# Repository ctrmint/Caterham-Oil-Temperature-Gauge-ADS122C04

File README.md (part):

# Caterham Dry-Sump Oil Temperature Gauge

> **Hardware target:** Waveshare **ESP32-S3-Touch-AMOLED-1.75**, standard SKU 31261 or cased SKU 31262 (466×466 AMOLED, CO5300 controller). This firmware **does not** target the 2.1-inch RGB-LCD board, the `-1.75C` model, or the GNSS `-G` version without adaptation.

An independent **oil-temperature gauge** for the Caterham 420R dry-sump tank's resistive temperature sender (potentially Caterham part **71167**). It needs no ECU wiring and no factory gauge modifications.
- **Measurement:** an **ADS122C04 24-bit I²C ADC** drives its own 250 µA current source through a reference resistor and then the sender, and compares the voltage across each. A dedicated ground-sense wire runs to the tank. So the reading is independent of the current's accuracy, the 3.3 V rail and ground offsets.
- **Hardware:** option A is three resistors on the ADC module's pins. Option B, recommended for the car, adds two filter capacitors across the pins. Either can be built without a board, on stripboard, or on a PCB. The display runs from USB-C.
- **Display:** the Waveshare board handles display, fault reporting and alarm presentation.

**Status: bench prototype, new front end.** Host unit tests pass and the firmware compiles without warnings under ESP-IDF 5.5.5 (normal and demo builds; versions pinned in `dependencies.lock`). On the bench, so far ([docs/VALIDATION.md](docs/VALIDATION.md)):
- The firmware runs on a Waveshare 31261, and the Classic and Sweep layouts pass in the demo build. Sweep's LED and the Needle and Trace layouts (#10–#12) build and pass the host tests, but haven't been checked on the screen yet.
- With the earlier front end, a bench sender stamped 6811 followed the Bosch 0 280 130 026 curve up to 89 °C against a reference probe. That is an indication about the sender, not a calibration.

**Still owed:**
- every bench test of the ADS122C04 front end ([hardware/WIRING.md](hardware/WIRING.md), bench steps), for whichever option is built;
- the measured Rref;
- a sender calibration up to 130 °C;
- every in-car test, including the engine-running noise check.

The firmware ships **without** a validated sender temperature curve, so it **shows ohms, not °C**, until you explicitly install measured calibration points. It is **not** a primary engine-protection instrument.

## Quick start

1. Read [hardware/BOM.md](hardware/BOM.md), [hardware/WIRING.md](hardware/WIRING.md), and [docs/SAFETY.md](docs/SAFETY.md) before wiring to the car.
2. On a **bench** (not in the vehicle), wire the circuit on a breadboard as in [hardware/WIRING.md](hardware/WIRING.md):
   - the ADS122C04 module to the display's socket (3.3V, G, and I²C on GPIO17/18);
   - Rref, R1 and R2;
   - a known test resistor in place of the sender.

   Check all voltages with a meter before connecting the display board.
3. Install **ESP-IDF 5.5.5** on Fedora as described in [docs/SETUP_FEDORA.md](docs/SETUP_FEDORA.md).
4. `idf.py set-target esp32s3 && idf.py build`, then flash through the board's `/dev/serial/by-id/usb-Espressif_*` port, never a bare `/dev/ttyACM0`, which can be another USB device: `idf.py -p "$(ls /dev/serial/by-id/usb-Espressif_*)" flash monitor` (see [Connect the board and flash](docs/SETUP_FEDORA.md#connect-the-board-and-flash)).
5. Boot with an **uncalibrated** sensor and confirm the display shows resistance and `CALIBRATION REQUIRED`; simulate open and short faults on the bench.
6. Independently characterise the exact sender, generate `main/CalibrationData.h`, rebuild, and verify °C against a reference thermometer. See [docs/CALIBRATION.md](docs/CALIBRATION.md).
7. For the car, solder the same parts to the module, fit the terminal strip and the box ([hardware/WIRING.md](hardware/WIRING.md), "Building it without a board"), and pass the bench steps, including the short-to-battery test. Then do the power, grounding, thermal, EMI and installation checks in [docs/INSTALLATION.md](docs/INSTALLATION.md).

`./scripts/test_host.sh` runs the host tests without any ESP32 hardware: the conversion, fault, alarm and display logic, the ADC's frame and CRC decoding, a circuit simulation of both front-end options, the stripboard and PCB checks, the calibration tool and the sender graph. GitHub Actions ([CI workflow](.github/workflows/ci.yml)) runs them, plus the normal and demo firmware builds, on every pull request and every push to `main`. `idf.py menuconfig` → **Caterham oil temperature gauge** → **Display synthetic sensor readings** runs a clearly marked BENCH DEMO; it must remain **off** for a real vehicle.

## Interface hardware

The front end is small enough to need no interface board. **Option A** is three resistors soldered to the Adafruit ADS122C04 module, with a 3-way terminal strip for the harness, all in a small box beside the display. **Option B**, recommended for the car, adds two 47 nF capacitors across the module's analogue pins. They filter interference near the ADC's 256 kHz sampling rate, and a shorted one gives a fault rather than a reading.

Each option has its own folder: [hardware/option-a](hardware/option-a/README.md) and [hardware/option-b](hardware/option-b/README.md). Each folder has:
- a description of the design;
- a complete parts list;
- a checked stripboard layout;
- a two-layer PCB, as a KiCad project with Gerbers.

[hardware/WIRING.md](hardware/WIRING.md) has the circuit, the build without a board and the bench steps.

| Part | Where | Why |
|---|---|---|
| Rref, 2.00 kΩ 0.1 % ≤ 25 ppm/°C | A0 to the sender wire | Carries the ADC's 250 µA current to the sender; the voltage across it is the reference. Set `kReferenceOhms` in `main/Config.h` to its measured value |
| R1, 2.2 kΩ | A1 to the sender wire | Sender high side. Limits fault current |
| R2, 2.2 kΩ | A2 to the ground-sense wire | Sender low side. Limits fault current |

The display runs from its own USB-C socket (in the car, an ignition-switched USB-C charger), and the module takes the display's 3.3 V. The harness is three wires: signal, ground sense, and a return wire from the gauge's ground to the tank bond stud.

## Display

There are twelve layouts of the same readings. Every one is on a pure black background (`#000000`), apart from White's white face, so the AMOLED's unused pixels are switched off.

* **Classic:** the title reads `OIL °C`, `OIL °F` or `OIL ohm`. The reading itself has no unit: large fixed-width digits, right-aligned so the ones digit stays in place, with a 3-digit reading centred on the screen (a four-character one such as `>284` or a 4-digit resistance uses the full width). The bottom line reads like `MAX 112  |  123 ohm` (maximum, then the sender resistance).
* **Sweep:** a 40-segment ring around the edge covering 30–130 °C, with scale labels 30…130 (86…266 in °F). Each lit segment shows the colour of its own place on the scale. Three large seven-segment digits, centred, sit over faint ghost segments; beyond the table a `<` or `>` sign appears just left of them. The unit sits above `OIL TEMP`, with the status, footer and demo text below. A resistance of 1000 Ω or more (uncalibrated only) shows as `--` in Sweep, and in full in Classic.
  * **The LED:** a round light at 6 o'clock, in the open bottom of the ring. It glows in the reading's colour and pulses while an alarm is latched: slowly at amber (`HIGH TEMPERATURE`, from 115 °C after the 2.5 s debounce) and faster at red. It's off on a sensor fault and in an uncalibrated build. The exception is a brief fault while an alarm is latched: the LED keeps pulsing, as the digits keep the alarm colour.
* **Needle:** an analogue dial. A white scale runs from lower left to lower right over 30–130 °C, with five numbers (30, 55, 80, 105, 130; 86…266 in °F), a tick between each pair and a pointer at each number. A red needle sits under a dark hub, with `OIL` above the unit at the bottom. There's no digital readout. The needle follows the same rules as Sweep's segments. It's hidden on a fault or when uncalibrated, rests at the start below the table, and sits at the table maximum above it. It moves smoothly, never past the reading, and doesn't sweep at power-up.
* **Trace:** the last 60 s, one point a second, newest on the right, as a thick line in the colours of the temperatures that made it: each point's colour, the same as the digits' at that moment, carries into the line around it. The newest point is a dot in its colour, or a ring when it's beyond the table. The window is 30 °C tall, with grid lines every 10 °C. It moves only when the newest point comes within 3 °C of its top or bottom, then re-centres. Thin amber and red lines mark 115 °C and 130 °C when they're in view. A fault or a reading below the table leaves a gap, never a carried-over value. The LED from Sweep sits at 6 o'clock under the status lines, with the same colours and pulses. There's no digital readout and, uncalibrated, no trace. The history is kept whichever layout is showing, and starts empty at power-up.
* **Tape:** an aircraft-style moving scale. The tape scrolls past a fixed pointer, so the scale moves rather than the needle. It shows 40 °C at a time, with ticks every degree and numbers every 10. A strip down its edge is in each temperature's colour, and amber and red bars mark 115 °C and 130 °C, so the hot zones come into view before the oil gets there. Past the ends of the calibration table the tape is hatched, with no numbers, and a small marker shows the session maximum. The reading sits in a window by the pointer: `>130` beyond the table, `--` on a fault, and ohms when uncalibrated. Under it is the rate of change, such as `▲ 2.4 °C/min`, `▼ 1.1 °C/min` or `STEADY` (under 0.5 °C/min). The rate comes from the last 30 one-second samples and is hidden unless all 30 are clean readings inside the table. The tape eases to each reading and is hidden on a fault or when uncalibrated.
* **OEM:** styled on the Caterham factory gauges. A black face in a dark rim, with a short grey tick every 10 °C from 50 to 130 °C and four numbers, 70, 90, 110 and 130 (158…266 in °F), mapped one for one onto the factory oil-pressure gauge's 0–8 bar. 90 is at 12 o'clock with the unit under it, and 50 has a tick but no number. An off-white tapered needle with a counterweight sits under a black hub. It follows Needle's rules on this span, so it rests at the start below 50 °C and below the table, sits at the end above it, and is hidden on a fault or when uncalibrated. It doesn't drop to the stop on a fault, because a resting needle would look like cold oil. There's no digital readout.
  * **The oil symbol is the LED:** an oil can with a thermometer below the hub, lit in the reading's colour and pulsing with the alarm, exactly as the LED on Sweep and Trace. It's dark grey when the LED would be off.
  * **CATERHAM:** the word shows at the bottom only while all is well: `NORMAL` or `OIL WARMING`, no alarm latched, a calibrated build that isn't the demo. Anything else (an alarm, a fault, a reading beyond the table, no calibration) puts the status line and footer in its place, so the dial changes visibly the moment something needs attention. The demo build never shows it.
* **White:** styled on a white-faced aftermarket oil-temperature gauge. A white face in a black ring, with a black tick every 2 °C from 40 to 140 °C (long at each 20, medium at the other tens) and six numbers, 40, 60, 80, 100, 120 and 140 (104…284 in °F), with 90 at 12 o'clock. A red tapered needle with a short counterweight sits under a black hub, with `OIL` and the unit below it. The needle follows Needle's rules on this span: it rests at the start below 40 °C and below the table, sits at the table maximum above it, and is hidden on a fault or when uncalibrated. There's no digital readout.
  * **The LED:** the same LED as on Sweep and Trace, at 6 o'clock in a round black socket, so its colours and glow show against the white. When it's off, the socket shows a dark-grey lens.
  * **The status window:** a black window at the bottom, running down into the ring, with the status line and footer in their usual colours. It shows only when something needs attention, which is exactly when OEM would hide `CATERHAM`, so the face stays clean while all is well. The demo build always shows it.
  * **Brightness:** a white face is much brighter than the dark layouts, especially at night. The firmware has no brightness control, so long-press to Night, or another dark layout, if it dazzles.
* **Night:** a dark layout for driving at night, with no ring, face or ticks. It's quiet while all is well and lights up the moment anything needs attention. The reading is at the centre of the screen in both states.
  * **Quiet:** while all is well (exactly when OEM shows `CATERHAM`), only the reading shows: whole degrees in a small font, in its usual colour at half brightness, with a dim unit under it. Under that, a small dim dot rises and falls every 2 s. It steps once per display update, so if the updates ever stopped the dot would stop too: a dark screen can't pass for a live one.
  * **Lit:** anything else (an alarm, a fault, a reading beyond the table, no calibration, and always in the demo build) shows Classic's large digits at full brightness with `OIL °C` above them, the status line and footer below, and the LED from Sweep and Trace under them. The status goes to `HIGH TEMPERATURE` at 115 °C, before the alarm's 2.5 s debounce, so the screen lights at the threshold.
* **Nixie:** the reading in four glowing nixie tubes, right-aligned in the same cells as Classic, so a 3-digit reading leaves the first tube dark. The numerals are drawn as thin glowing wires, always nixie orange, with the ten unlit numerals faint behind them as in a real tube. `<`, `>` and `-` are drawn the same way, and anything the tubes can't show is `--`. `OIL °C` sits above the tubes, with the status line, the footer and the LED from Sweep and Trace always shown below. Nixie orange is close to the alarm amber, so on this layout the status line (in the reading's colour) and the LED carry the colour, not the numerals.
* **Heritage:** a dial in the spirit of a 1960s instrument. A chrome-look bezel (lit from the upper left), a black face, and cream ticks and numbers on a short 90° sweep across the top: 50–130 °C, a tick every 5 °C (long at each 20), with 50, 90 and 130 numbered (122, 194, 266 in °F) and 90 at 12 o'clock. A slim cream needle with a short counterweight turns about a pivot below the centre, under a black boss with a chrome cap. It follows Needle's rules on this span, as OEM's does, and never points below the pivot. There's no digital readout.
  * **Under the pivot:** `OIL TEMP` and the unit while all is well, exactly as OEM shows `CATERHAM`, or the status line and footer in their place whenever anything needs attention.
  * **The lamp:** the LED from Sweep and Trace at 6 o'clock in a chrome surround, with a dark lens when it's off.
* **Track:** a data page for track days. At the top, the reading in its colour, with `MAX 121` (the session maximum, or `MAX >130` once it went above the table) and the rate of change (as on Tape) beneath it. Then a row for each band since power-up, each with a bar in the band's colour and the time spent there:
  * `<60`, `60-115`, `115-130`, `130+` (from the alarm thresholds; `<140`, `140-239`, `239-266`, `266+` in °F) and `--`, which is time with no temperature known: a fault, or a gap of more than 2 s between readings. A reading beyond the table counts towards the coldest or hottest band.
  * Each bar is its band's share of the time since power-up, so the bars add up to one full bar. Any time at all in a band shows as at least a sliver. Times read `m:ss`, then `1h05`, up to `99h59`. They start again from zero at each power-up and are counted whichever layout is showing.
  * The status line, the footer and the LED from Sweep and Trace sit below. Uncalibrated, only the ohms and the status show: no rows, no MAX and no rate.
* **Warm-up:** for the first minutes of a drive. A 270° ring like Classic's arc fills from 0 °C to the 60 °C warm threshold in the reading's colour, so it's full once the oil is warm and turns amber or red with the reading. Classic's large digits sit in the middle with `OIL °C` above, and the status line and footer below. There's no LED.
  * **The warm-up line:** while warming, the time since power-up and the rate of warming (as on Tape), such as `2:35    ▲ 3.1 °C/min`. At the first reading of 60 °C or more it becomes `WARM IN 6:12`, which stays for the rest of the power cycle even if the oil cools again. If the oil was already warm when the gauge started, it shows `WARM AT START`.
  * **On a fault the ring disappears altogether.** An empty ring would look like cold oil. Below the table the ring shows its empty track, because the oil is known to be cold. It never predicts when the oil will be warm. Uncalibrated, there's no ring and no warm-up line.

The status line and the footer are on every layout, so alarms and faults always show as text. On OEM they take the wordmark's place, on Heritage the legend's, on White they appear in a black window, and Night lights up with them, whenever anything needs attention.

**Colours:** the digits (except Nixie's, which are always nixie orange), the status text and Classic's arc are graduated by temperature, blending smoothly between bands: dark blue below 50 °C, light blue 50–69, green 70–95, yellow 96–105, amber 106–119 and red from 120 °C. The colour is never less severe than a latched alarm (amber at 115 °C, red at 130 °C, unchanged). A fault or an uncalibrated reading is amber.

Beyond the calibration table the reading shows `<min` or `>max` (for example `<20` or `>140`) and no temperature reading, and the unit stays in the label. Uncalibrated firmware shows `ohm` in every layout. There are no scale numbers, no lit segments, no LED (OEM's symbol stays dark grey, and White's socket and Heritage's lamp show their dark lens), no needle, no trace, no tape or rate, no Track rows, and no Warm-up ring or warm-up line.

**Changing layout:** press anywhere on the screen for at least 1 s (a long-press). Each press moves to the next layout: Classic, Sweep, Needle, Trace, Tape, OEM, White, Night, Nixie, Heritage, Track, Warm-up, then Classic again. A short tap or a swipe does nothing. The choice is stored in flash and restored at power-up; it is Classic on first boot, or if the stored choice is missing or can't be read.

**Choosing °F:** `idf.py menuconfig` → **Caterham oil temperature gauge** → **Display temperature unit**, then rebuild. °C is the default. The unit applies to the display only; the serial CSV log stays in °C.

## Wi-Fi

The gauge can join a Wi-Fi network or host it. It's off until you ask for it, and it can't delay a reading or touch the alarms: everything Wi-Fi runs in its own task below the measurement loop's priority.

* **One network, two ways:** when Wi-Fi is switched on, the gauge looks for the network named in `main/wifi_secrets.h`.
  * **Found:** it joins as a client. The panel shows `Joined <network>` and the address it was given.
  * **Not found:** it hosts that network itself, with the same name and password, at `192.168.4.1`. The panel shows `Hosting <network>`. A laptop set up for that network connects either way.
  * **Found but it can't join** (a wrong password, say): `Wifi failed` and `Can't join <network>`. It never hosts a second network with the same name.
  * **A joined network that drops** (driving away from home, say): it rejoins if it can, and hosts the network once it's gone.

* **The BOOT button** (the top side button) switches it. Each short press moves to the next state, and a black panel across the top of the screen confirms it for 3 s:
  * `Wifi Off` → `Wifi - Web On, UDP Off` → `Wifi - Web On, UDP On` → `Wifi - Web Off, UDP On` → `Wifi Off`.
  * States for features that aren't built in are skipped. With only the UDP stream built, presses go `Wifi Off` ↔ `Wifi - Web Off, UDP On`; with only the web page, `Wifi Off` ↔ `Wifi - Web On, UDP Off`.
  * While starting, the panel says `Wifi starting...` and `Looking for <network>`. Once up, it says `Joined` or `Hosting`, with the network and the gauge's address. `Wifi failed` shows in amber if it can't start.
  * The panel never covers the status lines or the LED on any layout, and the button never touches an alarm.
  * The state is saved and restored at power-up. A long press does nothing. Don't hold BOOT while powering up, or the board starts in flashing mode.
* **The web log page** (#32): open `http://<the address on the panel>/` in a phone's browser on the same network (`http://192.168.4.1/` when the gauge hosts it). It shows the live reading on a copy of the Sweep face, a chart of the session with the alarm thresholds, the time in each band, and a **Download CSV** button. It loads nothing from the internet, can't change anything on the gauge, and keeps its copy of the session on the phone through reloads and gauge restarts. The gauge keeps the last 8 hours for it from power-up. See [docs/WEB_PAGE.md](docs/WEB_PAGE.md).
* **The UDP data stream** (#33): four packets a second to the multicast group `239.10.10.10:5005`, send-only, for a laptop or Raspberry Pi on the network. Watch it with `python3 scripts/udp_listen.py`, a live terminal dashboard (add `--csv FILE` to log, or `--plain` for one line per packet). The packet format is in [docs/UDP_STREAM.md](docs/UDP_STREAM.md).
* **Setting it up:**
  1. Copy `main/wifi_secrets.example.h` to `main/wifi_secrets.h` and put in the network name (1–32 characters) and password (8–63, WPA2). Git ignores that file: never commit it.
  2. `idf.py menuconfig` → **Caterham oil temperature gauge** → **Wi-Fi (#32, #33, #34)** → switch on **Web log page**, **UDP data stream**, or both.
  3. Rebuild. A first build after creating the file picks it up by itself.

  Without the file, or with both off, a build never starts Wi-Fi. The button then says `Wifi failed - no settings` or `Wifi not built`.

Every output, from the display and the serial log to the UDP packet and the page's JSON and CSV, is listed side by side, with how each writes the same values, under [Outputs in docs/ARCHITECTURE.md](docs/ARCHITECTURE.md#outputs).

## Repository structure

```text
.
├── main/
│   ├── main.cpp                    # main sampling / display loop
│   ├── Config.h                    # reference resistor value, fault and warning settings
│   ├── CalibrationData.h           # fail-closed uncalibrated default
│   ├── core/                       # platform-independent resistance & temp math,
│   │                               # ADC frame/CRC decoding (AdcFrame.h),
│   │                               # plus display text (DisplayText.*), sweep ring,
│   │                               # LED and needle model (SweepModel.*), the trace's
│   │                               # history (TraceModel.*), the tape and rate of change
│   │                               # (TapeModel.*), the OEM and White dials
│   │                               # (OemModel.*, WhiteModel.*), Night's quiet
│   │                               # rule and heartbeat (NightModel.*), Nixie's
│   │                               # tubes and numerals (NixieModel.*), the
│   │                               # Heritage dial (HeritageModel.*), Track's
│   │                               # band times and bars (TrackModel.*), the
│   │                               # warm-up ring and clock (WarmupModel.*), the
│   │                               # UDP packet (UdpPacket.*), the web page's
│   │                               # log and JSON (WebLog.*), the Wi-Fi button
│   │                               # and panel (WifiChoice.*)
│   │                               # and layout choice/long-press
│   │                               # (LayoutChoice.*)
│   ├── hal/Ads122c04Source.*       # ADS122C04 over I²C (port 0, GPIO17/18)
│   ├── net/WifiNet.*               # the Wi-Fi network and UDP stream task (#33, #34)
│   ├── net/WebServer.*             # the web page's log, status and server (#32)
│   ├── web/index.html              # the web page, built into the firmware (#32)
│   ├── display/GaugeDisplay.*      # Waveshare BSP + LVGL 9 gauge; layout switching
│   │   ├── ClassicLayout.cpp       # Classic layout
│   │   ├── SweepLayout.cpp         # Sweep layout, with its LED
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
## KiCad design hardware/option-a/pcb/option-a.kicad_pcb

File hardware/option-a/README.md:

# Option A: the minimal front end

Option A is the simplest version of the gauge's front end: the ADS122C04 module's own current source, a reference resistor and two tap resistors. There's nothing else, so it needs no PCB at all, although a stripboard layout and a PCB are here too.

It's fine on the bench. **For the car, use [option B](../option-b/README.md)** unless option A passes the in-car noise check (step 14 in [WIRING.md](../WIRING.md)). Option B adds two filter capacitors and keeps everything else the same, including the firmware.

## The circuit

| Module pin | Connects to | Part |
|---|---|---|
| VIN, GND, SDA, SCL | the display's `3.3V`, `G`, `17`, `18` | the display lead |
| A0 | `SENDER`, through Rref | **Rref: 2.00 kΩ, 0.1 %, 25 ppm/°C or better** |
| A1 | `SENDER`, through R1 | R1: 2.2 kΩ, 1 % |
| A2 | the ground-sense wire, through R2 | R2: 2.2 kΩ, 1 % |
| A3, Ref+, Ref−, DRDY, !RST | nothing | |

**How it measures:**
- The ADC drives 250 µA out of A0, through Rref and then the sender, to the tank. It reads the voltage across each.
- The resistance is `Rs = Rref × Vs / Vref`. The current's ±6 % accuracy, the ADC's reference and the 3.3 V rail all cancel, so the reading is as good as Rref.
- **Measure Rref** and put its value in `kReferenceOhms` (`main/Config.h`).
- The ground-sense wire reads the tank's own potential, so a ground offset between the gauge and the tank cancels too.

**Faults:** every open joint, broken wire and short shows a fault, never a reading. The ADC's 10 µA burn-out source checks both taps every cycle. [WIRING.md](../WIRING.md) has the full list, the engineering calculations and the bench steps.

**What option A doesn't have:**
- **No input filter.** Interference near the ADC's 256 kHz sampling rate can reach the reading without a fault. Option B fixes this.
- **No clamp diodes or TVS.** At least 2 kΩ between every harness wire and the ADC holds a short to 14.4 V to about 5 mA per pin, within the chip's rating. That isn't load-dump protection, so the short-to-battery bench test (step 12) is owed.

## Three ways to build it

| Build | What it is | Where |
|---|---|---|
| **Without a board** | The three resistors soldered straight onto the module's pins, with a 3-way terminal strip for the harness | [WIRING.md](../WIRING.md), "Building it without a board" |
| **Stripboard** | 73.7 × 27.9 mm (28 holes × 10 strips): 11 track cuts, 3 wire links, two screw terminal blocks | [veroboard/](veroboard/): `layout.svg` and `ASSEMBLY.md` |
| **PCB** | 71 × 36 mm, two layers, plated through-hole, Micro-Fit connectors that lock | [pcb/](pcb/): the KiCad project, `fab/option-a-gerbers.zip` and renders |

[BOM.md](BOM.md) lists the parts for all three: the parts every build needs, then each build's own.

In every build, the module is **soldered in by its header pins, never socketed**, and Rref is measured before it goes in.

### Stripboard

- **J1, the display lead:** 1 3.3V, 2 G, 3 18 (SCL), 4 17 (SDA). The four strips run straight to the module's own pins.
- **J2, the sender harness:**
  - 1 signal wire to the sender;
  - 2 ground-sense wire;
  - 3 **empty**;
  - 4 return wire to the tank bond stud.
- **Upgrading:** option B's C1 and C2 holes (13,4–13,5 and 15,5–15,6) are left empty, so fitting the two capacitors turns this board into option B.

### PCB

- **J1, the display lead (Micro-Fit 2x3):**
  - 4 SDA (17), 5 SCL (18) and 6 3.3V each sit beside a ground (pins 1–3);
  - the three ground wires join at the display plug's `G` pin;
  - J1's grounds reach the module on the top copper, over the signal tracks.
- **J2, the sender harness (Micro-Fit 1x4):** the same as the stripboard's J2, with pin 3 empty.
- **Mis-plugging:** J1 and J2 are different sizes, so neither cable fits the other's header.
- **Mounting:** four M3 holes, 64 × 29 mm apart, and M2.5 nylon standoffs under the module's own holes.
- **Upgrading:** this board has no C1 or C2 pads. For option B, order the [option B PCB](../option-b/pcb/).

## Why the boards look the way they do

- **Return wire:** it lands on the board's ground, so the display lead needs only its four signals. The no-board build needs a fifth wire for it.
- **J2 pin 3 is empty, and no ground copper runs beside A1, A2, SENDER or SENSE.** A solder bridge from any of those to ground would give a believable wrong reading, not a fault. Two examples:
  - **SENSE to ground:** the tank offset adds straight into the sender's voltage.
  - **A1 to ground:** the measurement turns single-ended.

  The stripboard checker refuses a ground strip beside them. On the PCB, a DRC rule keeps their copper at least 1 mm from ground, and there's no ground pour; the closest they actually come is 2.5 mm.
- **R1 meets SENDER at J2 pin 1** by its own track, so it senses at the connector, not partway along the excitation current's path.

## Before you trust it

1. Measure Rref, and set `kReferenceOhms`.
2. Run bench steps 1–13 in [WIRING.md](../WIRING.md), including the tap checks, the pin-pair shorts and the short to battery.
3. Do the in-car noise check (step 14).
4. Calibrate the sender ([CALIBRATION.md](../../docs/CALIBRATION.md)).

Until then it's a bench prototype ([VALIDATION.md](../../docs/VALIDATION.md)).

## Files

Everything here except this README is generated by `scripts/boards/build.sh`, from `scripts/boards/`. That script runs KiCad 10.0.8 in its container (podman or docker).
- **The layouts:**
  - the circuit is `circuit.py`;
  - the stripboard is `vero_layout.py`;
  - the PCB placement and routing are `pcb_layout.py`.
- **Each build:**
  - checks the stripboard layout;
  - runs KiCad's ERC, and DRC with schematic parity;
  - confirms the schematic's netlist is the circuit;
  - writes `outputs.sha256`.
- **Tests:** `tests/test_boards.py` fails if any output is stale, and re-checks the circuit, the stripboard and the PCB's clearances independently.
- **Editing:** never edit the outputs by hand.

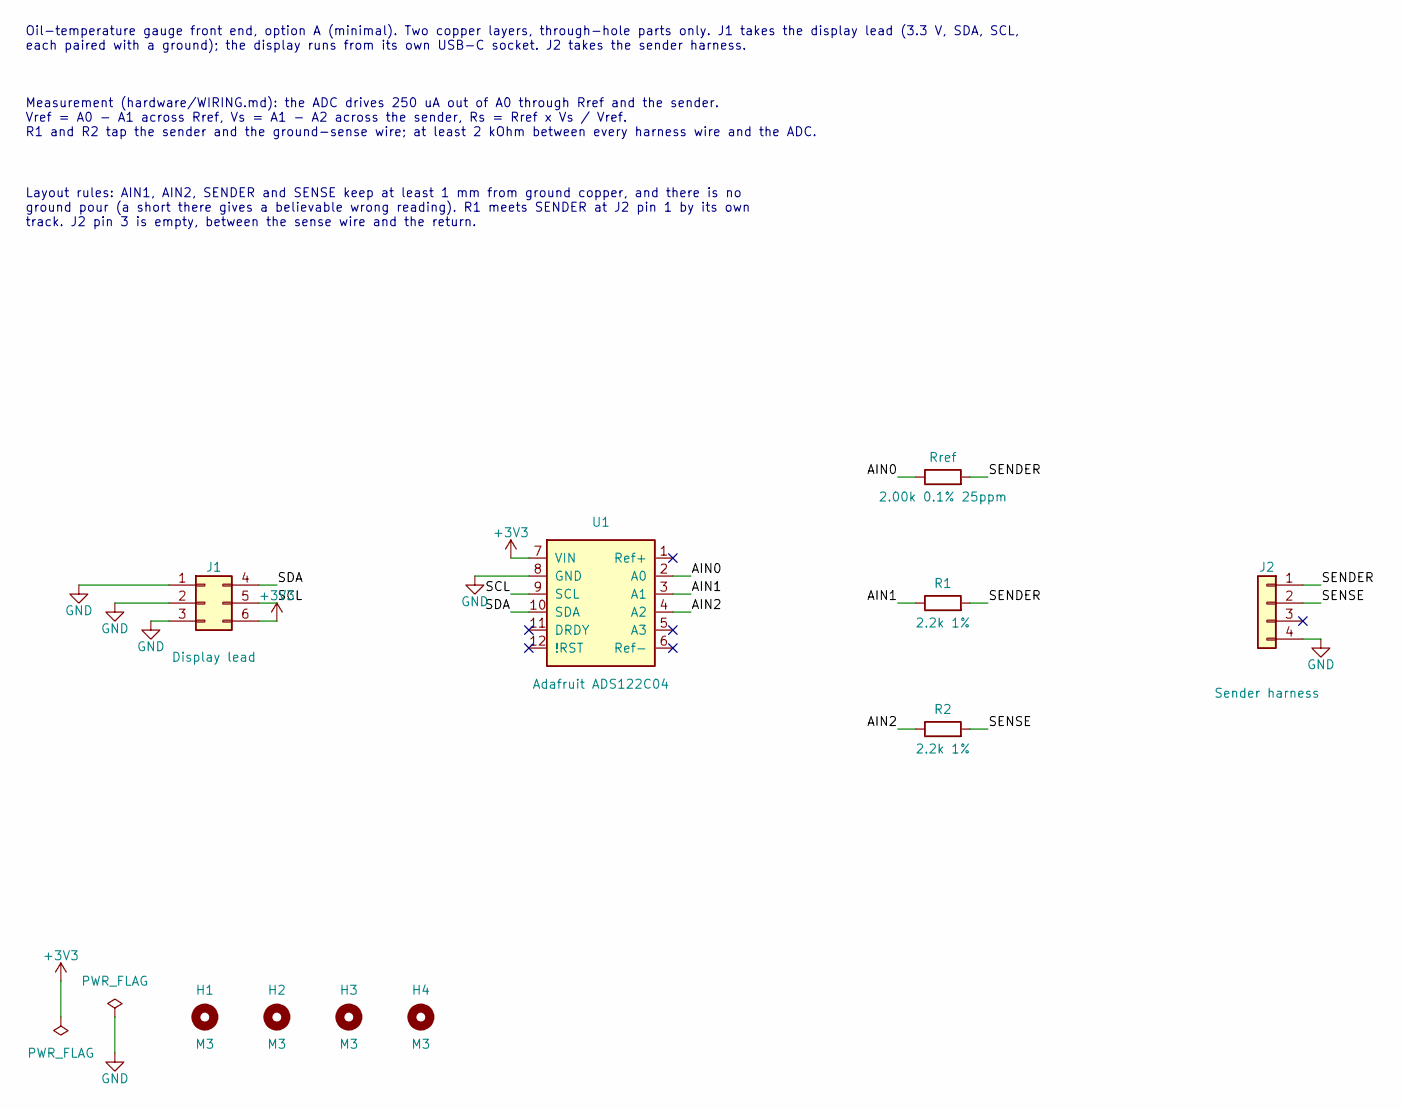
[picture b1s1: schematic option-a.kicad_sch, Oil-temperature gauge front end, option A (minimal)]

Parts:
H1, H2, H3, H4: M3; MountingHole_M3
J1: Display lead; MicroFit_2x03_RA; MPN 43045-0600; DigiKey_UK WM1815-ND
J2: Sender harness; MicroFit_1x04_RA; MPN 43650-0400; DigiKey_UK WM1862-ND
R1, R2: 2.2k 1%; R_P10.16mm
Rref: 2.00k 0.1% 25ppm; R_P10.16mm
U1: Adafruit ADS122C04; Adafruit_ADS122C04; MPN 6432

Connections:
+3V3: J1.6, U1.7 (VIN)
/AIN0: Rref.1, U1.2 (A0)
/AIN1: R1.1, U1.3 (A1)
/AIN2: R2.1, U1.4 (A2)
/SCL: J1.5, U1.9 (SCL)
/SDA: J1.4, U1.10 (SDA)
/SENDER: J2.1, R1.2, Rref.2
/SENSE: J2.2, R2.2
GND: J1.1, J1.2, J1.3, J2.4, U1.8 (GND)

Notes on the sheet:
Oil-temperature gauge front end, option A (minimal). Two copper layers, through-hole parts only. J1 takes the display lead (3.3 V, SDA, SCL, each paired with a ground); the display runs from its own USB-C socket. J2 takes the sender harness.
Layout rules: AIN1, AIN2, SENDER and SENSE keep at least 1 mm from ground copper, and there is no ground pour (a short there gives a believable wrong reading). R1 meets SENDER at J2 pin 1 by its own track. J2 pin 3 is empty, between the sense wire and the return.
Measurement (hardware/WIRING.md): the ADC drives 250 uA out of A0 through Rref and the sender. Vref = A0 - A1 across Rref, Vs = A1 - A2 across the sender, Rs = Rref x Vs / Vref. R1 and R2 tap the sender and the ground-sense wire; at least 2 kOhm between every harness wire and the ADC.

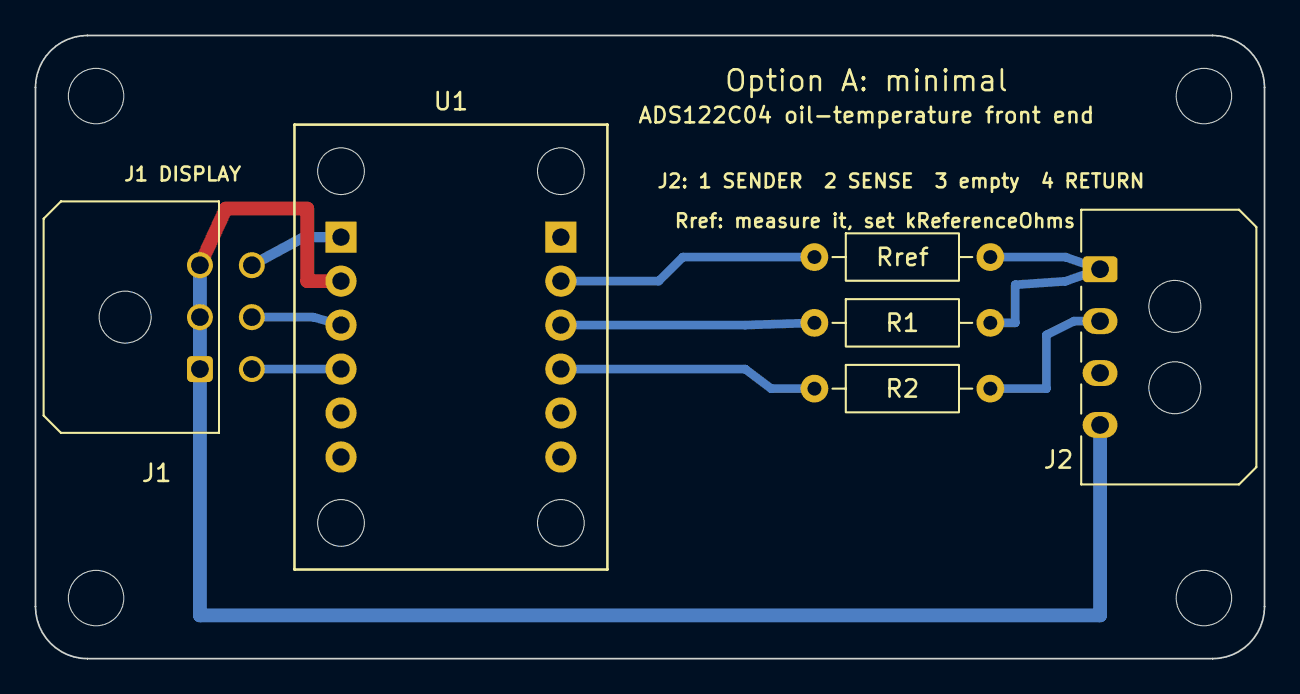
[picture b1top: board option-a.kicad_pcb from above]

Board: 2 copper layers, 71.0 x 36.0 mm, 10 parts (0 on the bottom side), 9 nets.

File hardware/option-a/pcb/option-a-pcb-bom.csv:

Qty,Ref,Item,Manufacturer,MPN,Digi-Key UK,Notes
1,U1,ADC module,Adafruit,6432,,ADS122C04 24-bit I2C ADC module (The Pi Hut SKU ADA6432). Solder it in by its header pins; never socket it
1,Rref,Reference resistor,,,,"Rref: 2.00 kOhm, 0.1 %, 25 ppm/C or better, metal film, 0.25 W, 0207. Measure it and put the value in kReferenceOhms"
2,"R1, R2",Tap resistors,,,,"2.2 kOhm, 1 %, metal film, 0.25 W, 0207"
1,,Display,Waveshare,ESP32-S3-Touch-AMOLED-1.75,,"Standard or -B; not 1.75C, 2.1 LCD or GNSS -G. Check the board revision and socket first"
1,,Display plug,Samtec,TSW-108-07-G-S,,8-way 2.54 mm gold pin header: the plug for the display case socket
1,,Display power,,,,"Ignition-switched USB-C charger rated for the car's transients, and a secured USB-C lead. Never 12 V to the display"
as needed,,Harness wire,,,,"0.5 mm2 (20 AWG): signal, ground sense and return, twisted together, away from ignition leads, the alternator and the exhaust"
1,,Ring terminal,,,,For the tank bond stud: the ground-sense and return wires land on it
1,,Sender spade connector,,,,"Insulated, retained against vibration; check it fits the sender"
1,,Box,,,,"Small, insulated, with strain reliefs or glands for both cables"
-,,Heat-shrink and sleeving,,,,For the harness and display-lead joints
1,,Sender,,,,The car's existing resistive oil-temperature sender (dry-sump tank). Confirm its type before relying on it
1,,PCB,,,,"Order from pcb/fab/option-a-gerbers.zip: 2 layers, 1.6 mm FR-4, 1 oz copper, plated holes, any standard prototype service"
1,J1,Display header,Molex,43045-0600,WM1815-ND,"Micro-Fit 3.0 2x3 right-angle header, tin, board lock"
1,,Display lead housing,Molex,43025-0600,WM1785-ND,Micro-Fit 3.0 2x3 receptacle housing (mates with J1)
1,J2,Harness header,Molex,43650-0400,WM1862-ND,"Micro-Fit 3.0 1x4 right-angle header, tin"
1,,Harness housing,Molex,43645-0400,WM1847-ND,Micro-Fit 3.0 1x4 receptacle housing (mates with J2)
9 (+spares),,Crimp terminals,Molex,43030-0007,WM1837-ND,"Micro-Fit 3.0 female crimp terminal, tin, 20-24 AWG"
1,,Crimp tool,Molex,63819-0000,,Micro-Fit 3.0 hand crimp tool (or a Micro-Fit ratchet crimper)
12,,Module header pins,,,,"2.54 mm header, both rows; a strip comes with the module"
1,,Display lead,,,,"3 twisted pairs, 24 AWG stranded, 20 cm or less: 3.3V+GND, SCL+GND, SDA+GND. The three grounds join at the display plug's G pin"
4,,Module standoffs,,,,"M2.5 x 2.5 mm nylon spacers with M2.5 nylon screws and nuts, under the module's four holes"
4,,Board screws,,,,"M3, into the box's bosses (holes 64 x 29 mm apart)"

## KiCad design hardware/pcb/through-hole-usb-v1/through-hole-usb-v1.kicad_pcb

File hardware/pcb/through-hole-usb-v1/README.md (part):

# through-hole-usb-v1: interface PCB

through-hole-usb-v1 is the third interface PCB (issue #54). It's [through-hole-v1](../through-hole-v1/README.md) without the 12 V supply: the display runs from its own USB-C socket, and this board takes its 3.3 V from the display over the cable.
- **One copper layer, through-hole parts only,** all hand-soldered.
- **It lives in its own 3D-printed box,** and a cable connects it to the display. The display doesn't plug into it.
- **It carries the same measurement and protection** as the other two boards.
- **A dedicated ground return comes back from the tank** on the harness connector, because a USB supply needn't share the car's ground (see Grounds, below).

**The firmware is unchanged:** the same ADS1115, address 0x48, GPIO17/18 and inputs.

**Status:** designed, with zero ERC and zero DRC findings. Not yet built or tested; the checks owed are listed below. Like the rest of the gauge, it's supplementary to the factory warnings ([docs/SAFETY.md](../../../docs/SAFETY.md)).

| | |
|---|---|
| Size | 65 × 62 mm, 3 mm corner radius, 4 × M3 mounting holes |
| Copper | **One layer** (bottom), 1 oz, ground pour. No vias, no top copper. |
| Tracks | 0.5 mm signals, 0.6 mm 3.3 V and the sender wire, 0.8 mm grounds; 0.3 mm minimum clearance |
| Pads | At least 0.6 mm of copper round each hole, because a single-sided board has unplated holes |
| Resistors | All lie flat at 10.16 mm: Vishay's MBB0207 datasheet asks for at least 10.0 mm between the leads |
| Parts | 24 through-hole parts plus 4 mounting holes. One part is the Adafruit ADS1115 module, soldered in. |
| Connectors | Two Molex Micro-Fit 3.0 right-angle headers, both along one edge, so both cables leave through one wall of the box |

## What's on it

- **ADC (U1):** the Adafruit ADS1115 breakout (product 1085).
  - The ADS1115 itself only comes in surface-mount packages, so the board takes the module.
  - Solder the module in by its header pins and hold it with nylon standoffs at its four holes. **Never socket it:** a lifting socket contact caused #39.
  - The module brings its own 10 kΩ I²C pull-ups and the 10 kΩ ADDR pull-down (address 0x48). Its A− (the ADC's ground) is joined to GND on the module.
- **Measurement and protection:** [WIRING.md](../../WIRING.md), with PR #34's protection, exactly as on through-hole-v1.
  - **Rp (R1)** is 470 Ω, 0.1 %, 25 ppm, 0.4 W.
  - **R2** is a Kelvin connection on Rp's top pad, on its own track.
  - **Each harness tap is two stages,** 1 kΩ then 1N4148 clamps to 3.3 V and GND then 1 kΩ: R3, D1, D2, R4 for A3, and R5, D3, D4, R6 for A1.
  - **D5** is a P6KE18A TVS on the signal wire.
  - **R7** is the 100 kΩ break-detect bias, on the harness side.
  - **C1–C3** are 100 nF C0G filters to ground.
  - Nothing is in series between Rp and the sender pin.
  - `tests/test_through_hole_usb_v1.py` checks all of this against the design table.
- **3.3 V:** it comes from the display on the cable. There's no 5 V on the cable and no regulator on the board.
  - A harness fault's current goes into the display's 2 A rail, which absorbs it, as on the other boards. With a wire at 14.4 V, that's about 34 mA (signal) or 10 mA (sense).
  - R8/R9 (3.3 kΩ) strengthen the I²C pull-ups for the cable, and C4 decouples 3.3 V at the module.
- **Test points:** TP1 and TP2 are grounds, TP2 on the track from the harness return; TP3 is 3.3 V.

## Power and grounds

**Power.** The display's own USB-C socket powers everything.
- In the car, use a USB-C charger (5 V, 1 A or more) on an **ignition-switched** 12 V circuit, so the gauge turns off with the ignition.
- On the bench, a USB-C supply or a laptop will do. Never connect the harness to the car while a laptop powers the display.
- Don't feed anything into the display's 5V pin: it's joined to the display's USB-C supply.

**Grounds.** On the other boards, the gauge's supply ground is wired to the chassis near the tank bond, and that carries the sender's current back. A USB supply makes no such promise: a power bank floats, and a car USB-C charger reaches the chassis only through its 12 V socket's wiring, somewhere else. So the harness brings its own ground back from the tank:
- **J2 pin 3, the ground return,** runs to the tank bond stud with the signal and ground-sense wires. The sender's excitation current, at most about 6.4 mA, comes back on it.
- **The ground-sense wire (pin 2) still measures the tank's own potential,** so the return wire's resistance doesn't enter the reading.
- **If the return wire breaks while the supply floats,** no sender current flows and the tank floats up to 3.3 V through Rp and the bias. The ground offset then reads about 3.3 V, so the gauge shows `GROUND FAULT`, never a reading.
- **If the charger's ground also reaches the chassis,** the gauge keeps measuring through that path. The ground-sense wire cancels the offset inside its window (−0.10 to +0.20 V), and outside it the gauge shows `GROUND FAULT`.
- **J2 pin 4** takes the harness screen (at this end only) or a second return wire to the same stud.
- **On the board:**
  - a track joins J2's return pins, past TP2, to J3's ground pins;
  - another joins the module's ground to J3;
  - the ground pour covers the rest.

## Connectors and cables

[BOM.md](BOM.md) lists every part with its manufacturer part number and the order codes that were confirmed. It also gives both connector pinouts and the display-cable wiring.

| | Connector | Pins |
|---|---|---|
| **J2** sender | Micro-Fit 1×4 right-angle (43650-0400), plug 43645-0400 | 1 sender signal, 2 ground sense, 3 ground return (to the tank bond stud), 4 GND (screen, or a second return) |
| **J3** display | Micro-Fit 2×3 right-angle (43045-0600), plug 43025-0600 | 1–3 GND, 4 3.3 V, 5 SCL, 6 SDA |

**The harness:** three 0.5 mm² wires to the tank, twisted together.
- The signal wire runs from pin 1 to the sender's spade.
- The ground-sense wire (pin 2) and the return (pin 3) both land on the tank bond stud.
- A 3-core screened cable also works, with its screen on pin 4 at this end only.

**The display cable** carries the I²C bus, so keep it **30 cm or shorter**, and use three twisted pairs of 24 AWG stranded wire:

| Pair | J3 pins | Display socket |
|---|---|---|
| 3.3 V and ground | 4 + 1 | 3.3V + G |
| SCL and ground | 5 + 2 | 18 + G |
| SDA and ground | 6 + 3 | 17 + G |

On J3 each signal pin sits directly above its ground pin.

- **Display end:** an 8-way 2.54 mm gold pin header (Samtec TSW-108-07-G-S) that plugs into the display case socket. Pin order, as the case label reads from the back: 18, 17, 16, RX, TX, 3.3V, G, 5V.
- **Wiring the header:**
  - Solder SCL to the pin labelled 18, SDA to 17 and 3.3 V to 3.3V.
  - Join the three ground wires into one short lead to G.
  - Leave 16, RX, TX and **5V** empty. The 5V pin carries the display's USB supply.
  - Sleeve each joint in heat-shrink, then pot the back of the header or fix it with hot-melt glue so the joints can't flex.
  - The header only friction-fits the socket, so clamp or tie the cable near the display, and the USB-C cable too.
- **Crimping:** both Micro-Fit plugs use 43030-0007 terminals, the same terminal and crimp tool as the other boards.

## The box

`box/through-hole-usb-v1-box.svg` is the drawing for the 3D-printed box. It gives:
- the outline;
- the four M3 hole positions, with the boss size that clears the parts;
- the two cable openings in the bottom wall, at their positions along the edge and their heights;
- the tallest parts.

## Ordering and assembly

1. **Board:** upload `fab/through-hole-usb-v1-gerbers.zip` and choose **1 layer**, 1.6 mm FR-4.
   - The zip holds the bottom copper, bottom mask, top legend, outline and drill file.
   - On a one-layer board the holes aren't plated; JLCPCB's one-layer service, for example, is "NPTH only". The pads are sized for that.
2. **Parts:** order from [BOM.md](BOM.md). Where no order code is given, order by the manufacturer part number.
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
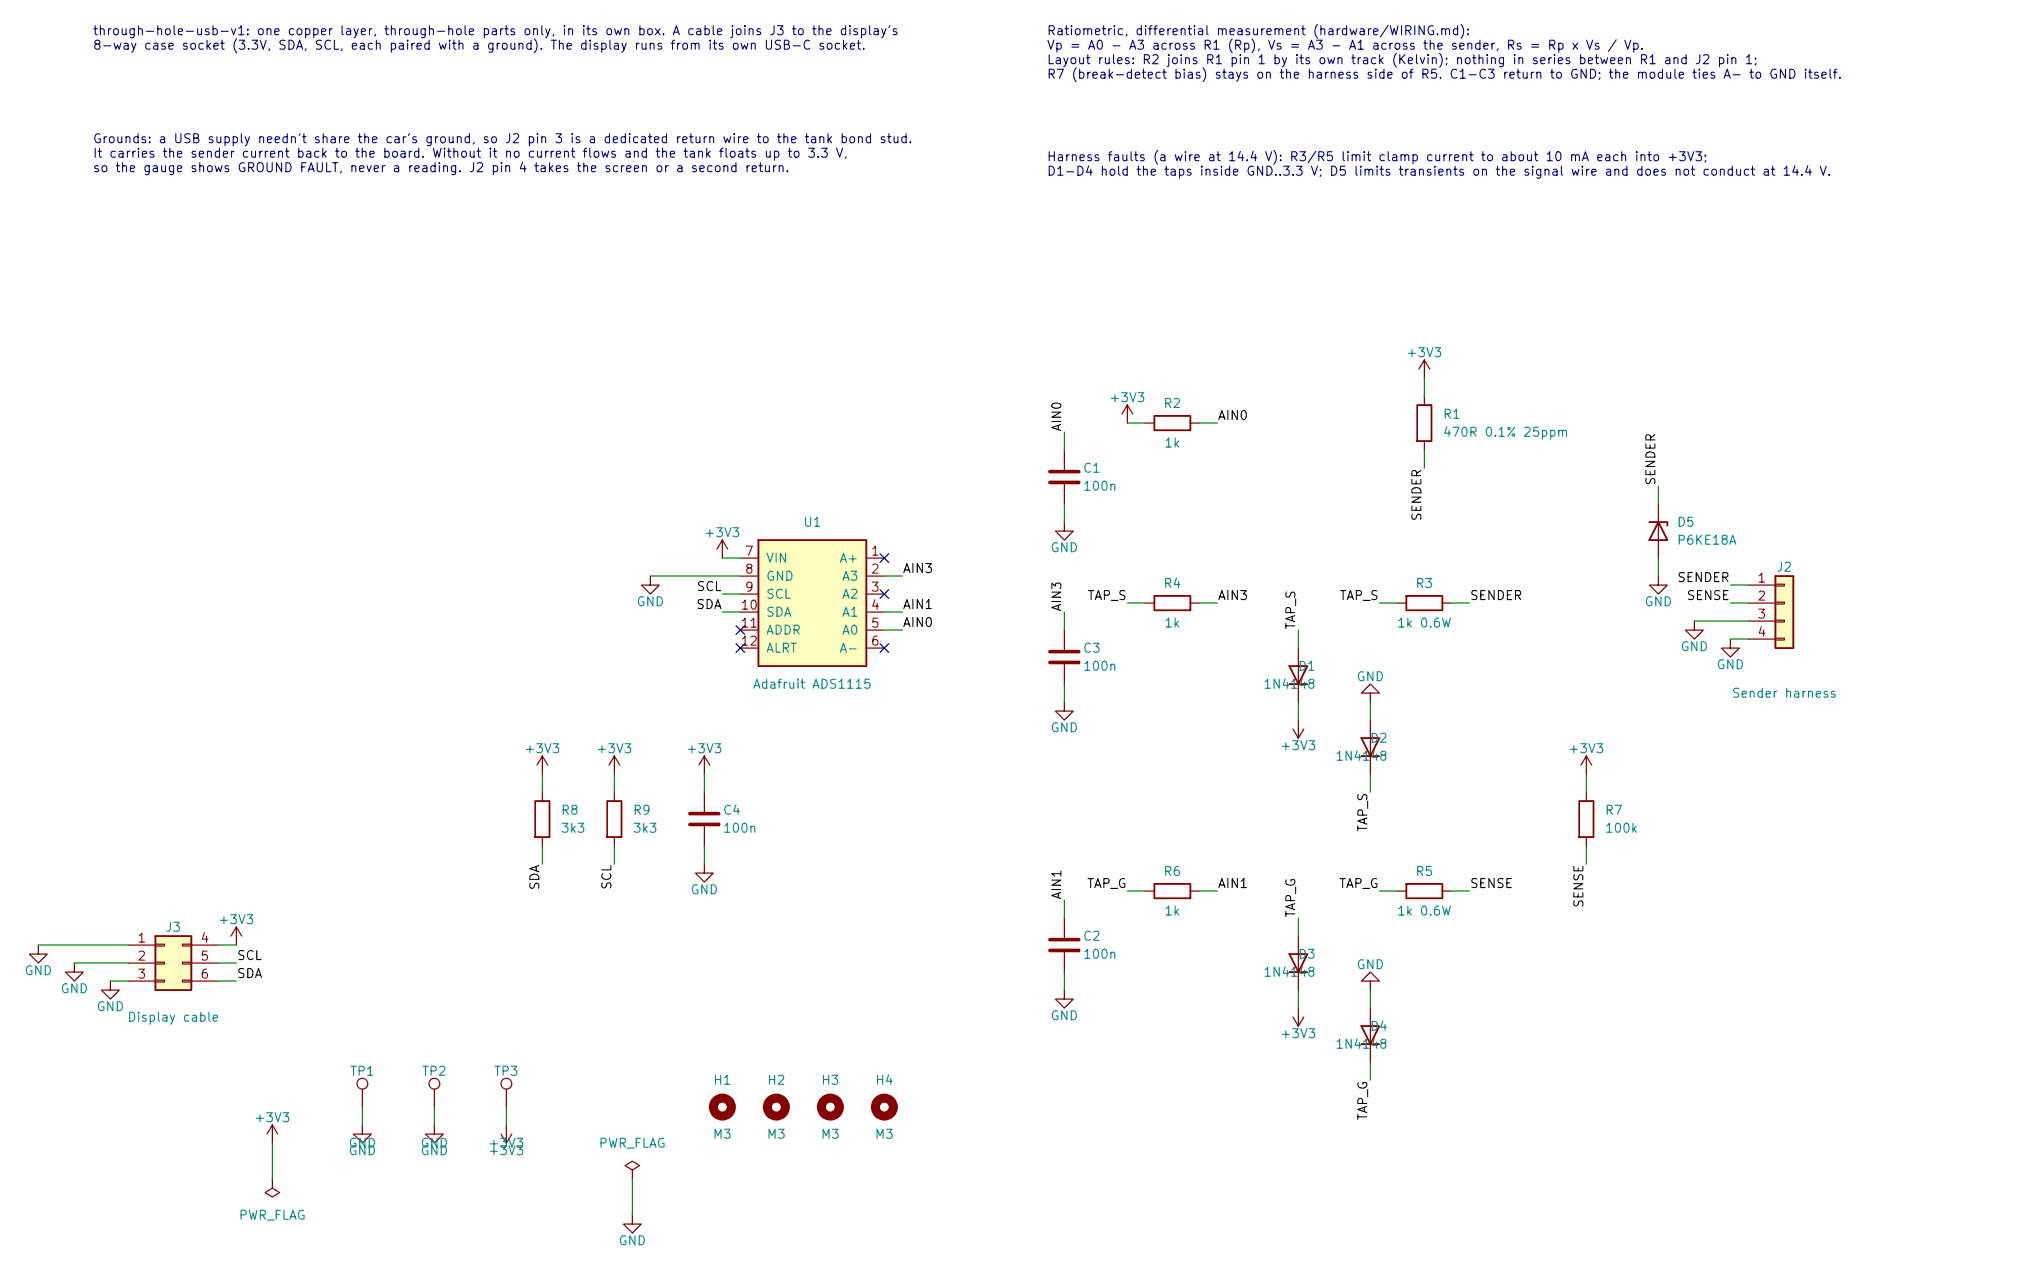
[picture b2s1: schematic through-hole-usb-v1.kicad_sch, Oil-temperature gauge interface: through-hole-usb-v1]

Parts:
C1, C2, C3, C4: 100n; C_P5.00mm; MPN FG26C0G1H104JNT06; DigiKey_UK 445-173396-1-ND
D1, D2, D4: 1N4148; D_DO-35_P7.62mm; MPN 1N4148-TAP; DigiKey_UK 1N4148-TAPCT-ND
D3: 1N4148; D_DO-35_P12.70mm; MPN 1N4148-TAP; DigiKey_UK 1N4148-TAPCT-ND
D5: P6KE18A; D_DO-15_P12.70mm; MPN P6KE18A-E3/54; DigiKey_UK P6KE18A-E3/54GICT-ND
H1, H2, H3, H4: M3; MountingHole_M3
J2: Sender harness; MicroFit_1x04_RA; MPN 43650-0400; DigiKey_UK WM1862-ND
J3: Display cable; MicroFit_2x03_RA; MPN 43045-0600; DigiKey_UK WM1815-ND
R1: 470R 0.1% 25ppm; R_P10.16mm; MPN MBB0207VD4700BC100; DigiKey_UK 56-MBB0207VD4700BC100CT-ND
R2, R4, R6: 1k; R_P10.16mm; MPN MBB02070C1001FCT00; DigiKey_UK BC3566CT-ND
R3, R5: 1k 0.6W; R_P10.16mm; MPN MBB02070C1001FCT00; DigiKey_UK BC3566CT-ND
R7: 100k; R_P10.16mm; MPN MBB02070C1003FCT00; DigiKey_UK BC3571CT-ND
R8, R9: 3k3; R_P10.16mm; MPN MBB02070C3301FCT00; DigiKey_UK BC3743CT-ND
TP1, TP2: GND; TestPoint; MPN 5001; DigiKey_UK 36-5001-ND
TP3: +3V3; TestPoint; MPN 5001; DigiKey_UK 36-5001-ND
U1: Adafruit ADS1115; Adafruit_ADS1115_STEMMA_QT; MPN 1085

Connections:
+3V3: C4.1, D1.1 (K), D3.1 (K), J3.4, R1.1, R2.1, R7.1, R8.1, R9.1, TP3.1, U1.7 (VIN)
/AIN0: C1.1, R2.2, U1.5 (A0)
/AIN1: C2.1, R6.2, U1.4 (A1)
/AIN3: C3.1, R4.2, U1.2 (A3)
/SCL: J3.5, R9.2, U1.9 (SCL)
/SDA: J3.6, R8.2, U1.10 (SDA)
/SENDER: D5.1 (K), J2.1, R1.2, R3.1
/SENSE: J2.2, R5.1, R7.2
/TAP_G: D3.2 (A), D4.1 (K), R5.2, R6.1
/TAP_S: D1.2 (A), D2.1 (K), R3.2, R4.1
GND: C1.2, C2.2, C3.2, C4.2, D2.2 (A), D4.2 (A), D5.2 (A), J2.3, J2.4, J3.1, J3.2, J3.3, TP1.1, TP2.1, U1.8 (GND)

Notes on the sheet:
through-hole-usb-v1: one copper layer, through-hole parts only, in its own box. A cable joins J3 to the display's 8-way case socket (3.3V, SDA, SCL, each paired with a ground). The display runs from its own USB-C socket.
Grounds: a USB supply needn't share the car's ground, so J2 pin 3 is a dedicated return wire to the tank bond stud. It carries the sender current back to the board. Without it no current flows and the tank floats up to 3.3 V, so the gauge shows GROUND FAULT, never a reading. J2 pin 4 takes the scre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
Harness faults (a wire at 14.4 V): R3/R5 limit clamp current to about 10 mA each into +3V3; D1-D4 hold the taps inside GND..3.3 V; D5 limits transients on the signal wire and does not conduct at 14.4 V.
Ratiometric, differential measurement (hardware/WIRING.md): Vp = A0 - A3 across R1 (Rp), Vs = A3 - A1 across the sender, Rs = Rp x Vs / Vp. Layout rules: R2 joins R1 pin 1 by its own track (Kelvin); nothing in series between R1 and J2 pin 1; R7 (break-detect bias) stays on the harness side of R5. C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

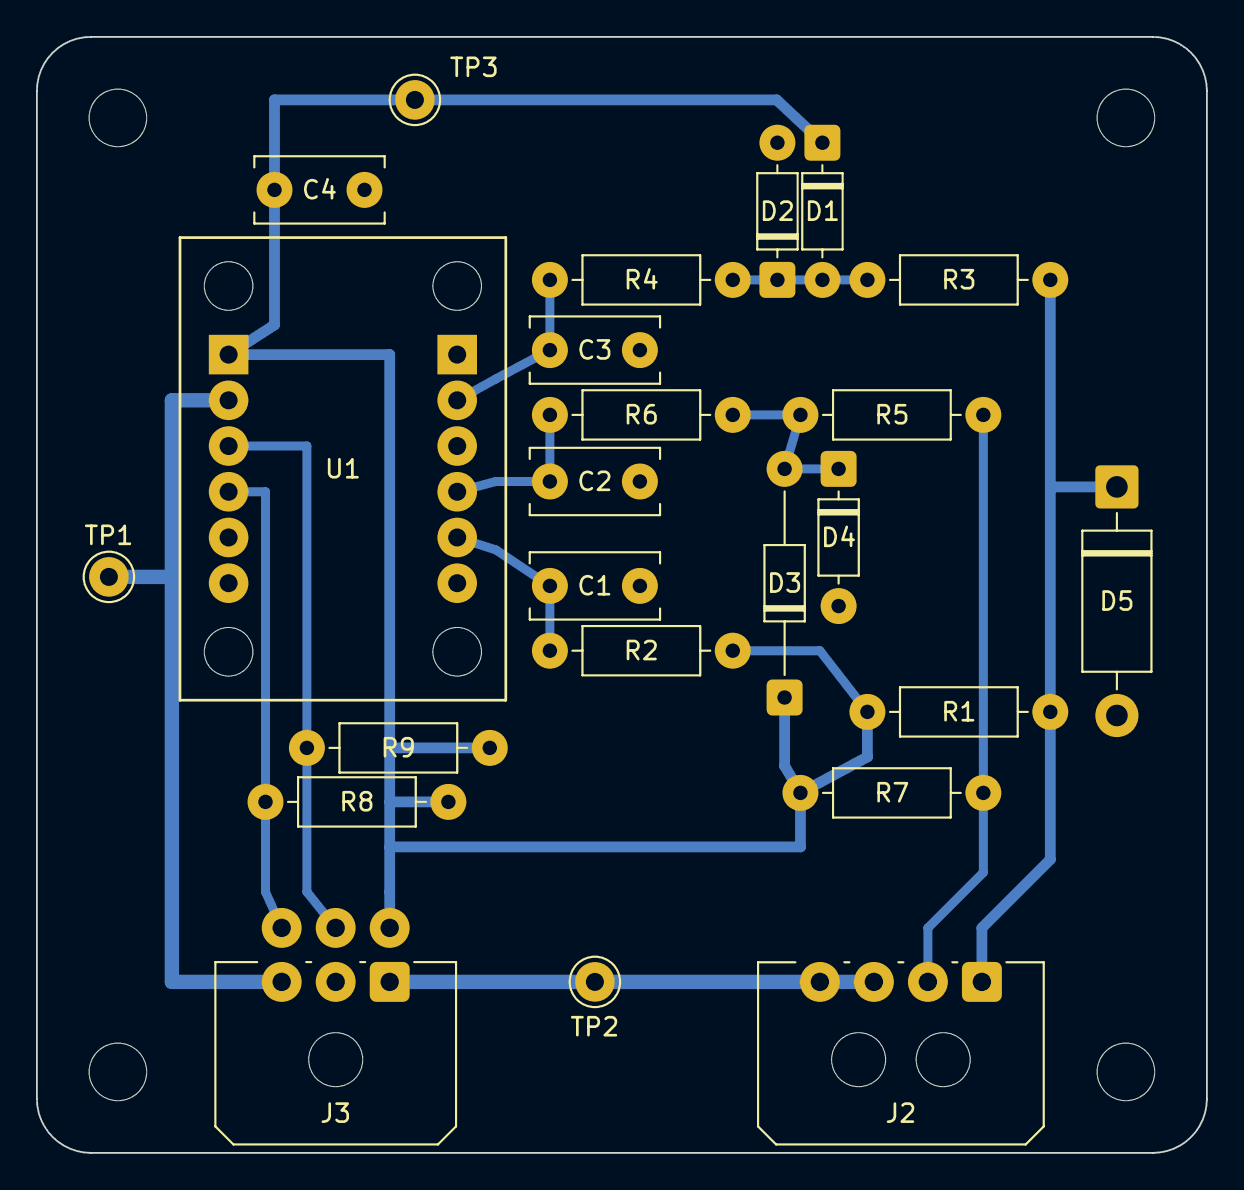
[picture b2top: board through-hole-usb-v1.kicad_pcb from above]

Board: 2 copper layers, 65.0 x 62.0 mm, 28 parts (0 on the bottom side), 11 nets.

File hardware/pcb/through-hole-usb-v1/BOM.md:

# through-hole-usb-v1: parts list

Every part for the through-hole-usb-v1 interface board, its cables and its box. The same list is in `through-hole-usb-v1-bom.csv`. Everything is through-hole and hand-soldered.

Generated by `generator/outputs.py` from `generator/design.py`; edit that, not this file, then run `build.sh`. Part numbers were checked against manufacturer datasheets and distributor pages on 2026-11-15. Order codes are Digi-Key UK (stock seen then); Farnell and RS carry most parts too.

## On the board

| Ref | Qty | Value | Package | Manufacturer | MPN | Digi-Key UK | Notes |
|---|---:|---|---|---|---|---|---|
| J2 | 1 | Sender harness | Micro-Fit 1x4 right-angle | Molex | `43650-0400` | WM1862-ND | Micro-Fit 3.0 1x4 right-angle header, tin; sender harness with its ground return |
| J3 | 1 | Display cable | Micro-Fit 2x3 right-angle | Molex | `43045-0600` | WM1815-ND | Micro-Fit 3.0 2x3 right-angle header, tin, board lock; display cable |
| U1 | 1 | Adafruit ADS1115 | Module, 2 x 6 pins | Adafruit | `1085` | - | ADS1115 breakout (STEMMA QT). Solder its header pins into the board, with 2.5 mm M2.5 nylon standoffs at its four holes |
| R1 | 1 | 470R 0.1% 25ppm | Axial 0207, 10.16 mm | Vishay | `MBB0207VD4700BC100` | 56-MBB0207VD4700BC100CT-ND | Rp: 470R 0.1% 25 ppm/K, 0207, 0.4 W; measure it before fitting (kPullUpOhms) |
| R2, R4, R6 | 3 | 1k | Axial 0207, 10.16 mm | Vishay | `MBB02070C1001FCT00` | BC3566CT-ND | 1k 1% 0.6 W metal film, 0207 |
| R3, R5 | 2 | 1k 0.6W | Axial 0207, 10.16 mm | Vishay | `MBB02070C1001FCT00` | BC3566CT-ND | 1k 1% 0.6 W metal film, 0207 (about 0.11 W if a harness wire reaches 14.4 V) |
| R7 | 1 | 100k | Axial 0207, 10.16 mm | Vishay | `MBB02070C1003FCT00` | BC3571CT-ND | 100k 1% 0.6 W; break-detect bias on the sense wire |
| R8, R9 | 2 | 3k3 | Axial 0207, 10.16 mm | Vishay | `MBB02070C3301FCT00` | BC3743CT-ND | 3k3 1% 0.6 W; I2C pull-up for the cable (the module adds 10k) |
| C1, C2, C3, C4 | 4 | 100n | Radial, 5 mm | TDK | `FG26C0G1H104JNT06` | 445-173396-1-ND | 100n 5% 50 V C0G, 5 mm leads |
| D1, D2, D4 | 3 | 1N4148 | DO-35 | Vishay | `1N4148-TAP` | 1N4148-TAPCT-ND | Small-signal diode, DO-35, 25 nA max leakage at 20 V, 25 C |
| D3 | 1 | 1N4148 | DO-35, 12.7 mm | Vishay | `1N4148-TAP` | 1N4148-TAPCT-ND | Small-signal diode, DO-35, 25 nA max leakage at 20 V, 25 C |
| D5 | 1 | P6KE18A | DO-15 | Vishay | `P6KE18A-E3/54` | P6KE18A-E3/54GICT-ND | TVS 600 W, 15.3 V standoff, unidirectional, DO-15; signal wire |
| TP1, TP2 | 2 | GND | Test loop | Keystone | `5001` | 36-5001-ND | Test point loop, black, 1.0 mm hole |
| TP3 | 1 | +3V3 | Test loop | Keystone | `5001` | 36-5001-ND | Test point loop, black, 1.0 mm hole |

## Connectors, cables, box hardware (not on the board)

| Item | Qty | Manufacturer | MPN | Digi-Key UK | Notes |
|---|---:|---|---|---|---|
| Harness plug housing (mates with J2) | 1 | Molex | `43645-0400` | WM1847-ND | Micro-Fit 3.0 1x4 receptacle housing (Molex calls it a receptacle; its 43640 "plug" is a different part) |
| Display-cable plug housing (mates with J3) | 1 | Molex | `43025-0600` | WM1785-ND | Micro-Fit 3.0 2x3 receptacle housing |
| Crimp terminals | 10 (+spares) | Molex | `43030-0007` | WM1837-ND | Tin, loose piece, for both housings; 20-24 AWG (0.5-0.2 mm2), insulation 1.42-1.85 mm |
| Crimp tool | 1 | Molex | `63819-0000` | - | Or a Micro-Fit ratchet crimper (as the other boards) |
| Display end of the cable | 1 | Samtec | `TSW-108-07-G-S` | - | 8-way 2.54 mm gold pin header, wired by hand (see README) and pushed into the display case socket |
| Display cable | 30 cm or less | - | `3 twisted pairs, 24 AWG stranded` | - | Pairs: 3.3V+GND, SCL+GND, SDA+GND. Keep it short: it carries the I2C bus. No 5 V wire |
| Display power | 1 | - | `USB-C supply, 5 V, 1 A or more` | - | In the car, a USB-C charger on an ignition-switched 12 V circuit; on the bench, a USB-C supply or a laptop. It plugs into the display, not this board |
| Module standoffs | 4 | - | `M2.5 x 2.5 mm nylon spacer, M2.5 nylon screws and nuts` | - | Hold the ADS1115 module down in a vibrating car |
| Board mounting | 4 | - | `M3 screws into the box's bosses` | - | See box/through-hole-usb-v1-box.svg |
| Harness wire | as needed | - | `0.5 mm2 (20 AWG)` | - | Three wires to the tank, twisted together: signal (J2 pin 1), ground sense (pin 2) and ground return (pin 3). Or a 3-core screened cable, screen to J2 pin 4 at this end only |

## Connector pinouts

**J2, sender harness (Micro-Fit 3.0, 1x4)**

| Pin | Net | Wire to |
|---:|---|---|
| 1 | SENDER | Sender spade terminal (signal) |
| 2 | SENSE | Ground-sense wire to the tank bond stud |
| 3 | GND | Ground return to the tank bond stud (required: the board's ground reference) |
| 4 | GND | Harness screen at this end only, or a second return wire to the same stud |

**J3, display cable (Micro-Fit 3.0, 2x3)**

| Pin | Net | Wire to |
|---:|---|---|
| 1 | GND | Display G (paired with 3.3 V, pin 4) |
| 2 | GND | Display G (paired with SCL, pin 5) |
| 3 | GND | Display G (paired with SDA, pin 6) |
| 4 | +3V3 | Display 3.3V (supplied by the display) |
| 5 | SCL | Display 18 (SCL) |
| 6 | SDA | Display 17 (SDA) |

**Display cable** (J3 to the display's 8-way case socket, left to right seen from the back):

| Case label | Net | J3 pin |
|---|---|---|
| 18 | SCL | 5 |
| 17 | SDA | 6 |
| 16 | - | not connected |
| RX | - | not connected |
| TX | - | not connected |
| 3.3V | +3V3 | 4 |
| G | GND | 1, 2, 3 |
| 5V | - | not connected |

Leave the display's 5V pin unconnected: it carries the display's USB-C supply, and this board doesn't use it.

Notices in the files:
README.md:
License:
MIT, see [LICENSE](LICENSE). Classic's digits are a bitmap font generated from Montserrat Medium (SIL Open Font License 1.1); the licence and the generation record (in the header of the generated file) are in [main/display/fonts/](main/display/fonts/). Third-party libraries are **not vendored** and keep their own licenses when installed by the Espressif component manager.
